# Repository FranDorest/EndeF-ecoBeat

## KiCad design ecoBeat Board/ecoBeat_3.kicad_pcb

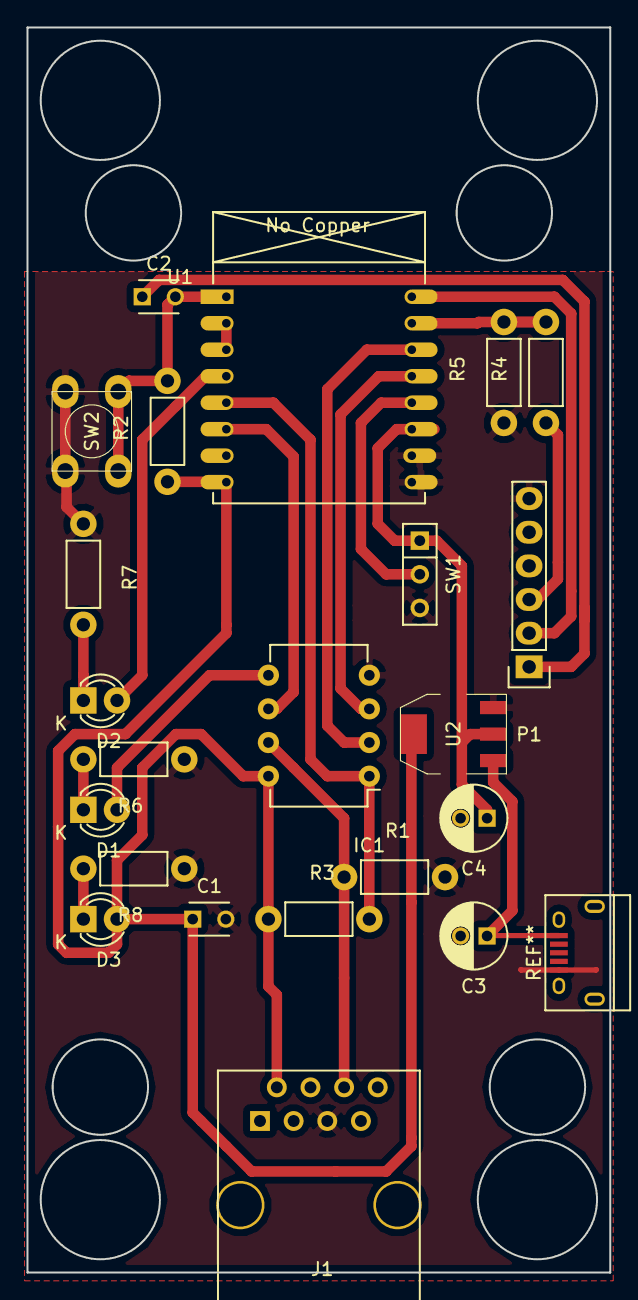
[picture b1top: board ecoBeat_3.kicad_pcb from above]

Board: 2 copper layers, 44.0 x 94.0 mm, 22 parts (0 on the bottom side), 19 nets.

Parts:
C1: 100nF; C_Disc_D3_P2.5
C2: C; C_Disc_D3_P2.5
C3, C4: 10uF; C_Radial_D5_L11_P2
D1, D2, D3: LED; LED-3MM
IC1: ATTINY85-P; DIP-8_W7.62mm
J1: RJ45; RJ45_8
P1: CONN_01X06; Pin_Header_Straight_1x06
R1, R2, R3: 10k; Resistor_Horizontal_RM7mm
R4: 6.8k; Resistor_Horizontal_RM7mm
R5: 12k; Resistor_Horizontal_RM7mm
R6, R7, R8: 220; Resistor_Horizontal_RM7mm
SW1: SWITCH_INV; SW_Micro_SPST
SW2: SW_PUSH; SW_PUSH_SMALL
U1: ESP-12E; ESP-07v2
U2: AP1117D33; SOT-223

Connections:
ESPRST: C2.2, R2.2, SW2.1, U1.1
GND: C1.2, C3.2, C4.2, IC1.4, J1.5, P1.6, R1.2, R5.1, R6.1, R7.1, R8.1, SW1.3, SW2.2, U1.9, U1.10, U2.1
INT1: IC1.6, U1.6
L1: D1.2, IC1.5
L2: D2.2, U1.4
unnamed: C2.1, P1.1
unnamed: C3.1, U2.3
unnamed: D1.1, R6.2
unnamed: D2.1, R7.2
unnamed: D3.1, R8.2
unnamed: IC1.7, J1.6, R1.1
unnamed: P1.3, R4.1
unnamed: SW1.2, U1.12
RSTTINY: IC1.1, R3.2, U1.5
RX1: IC1.2, U1.13
RXD: R4.2, R5.2, U1.15
TX1: IC1.3, U1.14
TXD: P1.2, U1.16
VCC: C1.1, C4.1, D3.2, IC1.8, J1.2, R2.1, R3.1, SW1.1, U1.2, U1.3, U1.8, U1.11, U2.2

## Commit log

2018-02-20 creado ecoBeat
2018-02-20 firmware subido
2018-02-20 nuevo soft attiny
2018-02-20 SoftwareSerial a 57600b
2018-02-20 SoftwareSerial a 9600b
2018-02-27 board 2
2018-02-27 attiny tx <-> rx
2018-02-28 rev2
2018-03-01 get ip
